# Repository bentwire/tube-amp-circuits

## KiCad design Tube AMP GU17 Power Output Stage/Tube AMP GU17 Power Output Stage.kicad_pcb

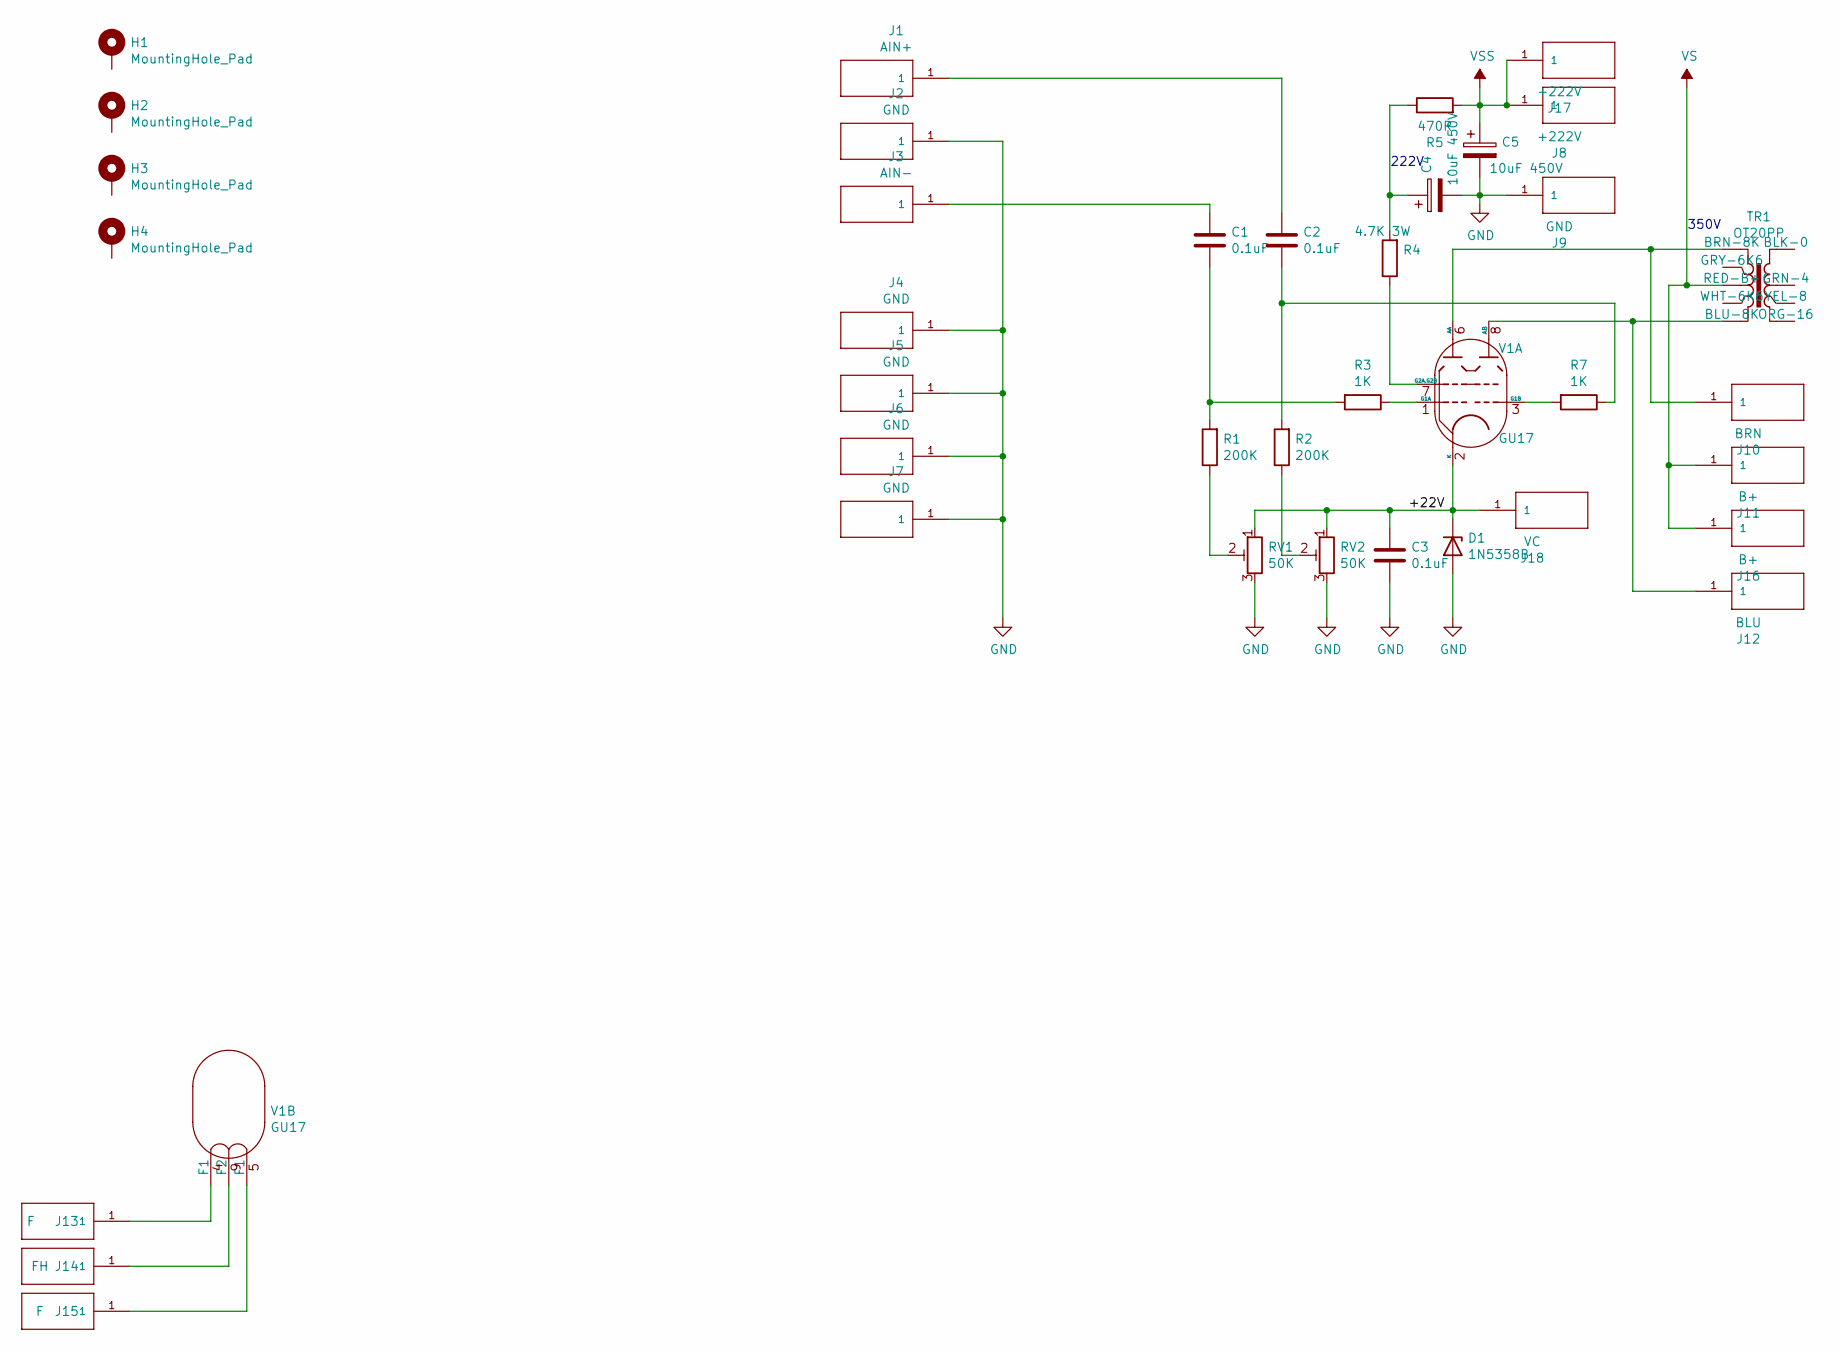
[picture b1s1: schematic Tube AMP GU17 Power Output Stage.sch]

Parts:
C1, C2, C3: 0.1uF; C_Rect_L7.2mm_W2.5mm_P5.00mm_FKS2_FKP2_MKS2_MKP2; MPN MKS2D031001A00MSSD
C4, C5: 10uF 450V; CP_Radial_D12.5mm_P5.00mm; MPN UCS2W100MHD
D1: 1N5358B; D_DO-201_P15.24mm_Horizontal
H1, H2, H3, H4: MountingHole_Pad; MountingHole_3.2mm_M3_Pad_Via
J1: AIN+; MILMAX_2501-2-00-80-00-00-07-0
J2, J4, J5, J6, J7, J9: GND; MILMAX_2501-2-00-80-00-00-07-0
J3: AIN-; MILMAX_2501-2-00-80-00-00-07-0
J8, J17: +222V; MILMAX_2501-2-00-80-00-00-07-0
J10: BRN; MILMAX_2501-2-00-80-00-00-07-0
J11, J16: B+; MILMAX_2501-2-00-80-00-00-07-0
J12: BLU; MILMAX_2501-2-00-80-00-00-07-0
J13, J15: F; MILMAX_2501-2-00-80-00-00-07-0
J14: FH; MILMAX_2501-2-00-80-00-00-07-0
J18: VC; MILMAX_2501-2-00-80-00-00-07-0
R1, R2: 200K; R_Axial_DIN0207_L6.3mm_D2.5mm_P10.16mm_Horizontal
R3, R7: 1K; R_Axial_DIN0207_L6.3mm_D2.5mm_P10.16mm_Horizontal
R4: 4.7K 3W; R_Axial_DIN0414_L11.9mm_D4.5mm_P20.32mm_Horizontal
R5: 470R; R_Axial_DIN0414_L11.9mm_D4.5mm_P20.32mm_Horizontal
RV1, RV2: 50K; Potentiometer_Bourns_3296W_Vertical
TR1: OT20PP
V1: GU17; B9A-PCB-21

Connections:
/+22V: C3.1, D1.1 (K), J18.1, RV1.1, RV2.1, V1.2 (K)
GND: C3.2, C4.2, C5.2, D1.2 (A), J2.1, J4.1, J5.1, J6.1, J7.1, J9.1, RV1.3, RV2.3
unnamed: C1.1, J3.1
unnamed: C1.2, R1.2, R3.2
unnamed: C2.1, J1.1
unnamed: C2.2, R2.2, R7.1
unnamed: C4.1, R4.2, R5.1
unnamed: J10.1, TR1.1 (BRN-8K), V1.6 (AA)
unnamed: J12.1, TR1.5 (BLU-8K), V1.8 (AB)
unnamed: J13.1, V1.4 (F1)
unnamed: J14.1, V1.9 (F2)
unnamed: J15.1, V1.5 (F1)
unnamed: R1.1, RV1.2
unnamed: R2.1, RV2.2
unnamed: R3.1, V1.1 (G1A)
unnamed: R4.1, V1.7 (G2A,G2B)
unnamed: R7.2, V1.3 (G1B)
VS: J11.1, J16.1, TR1.3 (RED-B+)
VSS: C5.1, J8.1, J17.1, R5.2

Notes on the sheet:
222V
350V

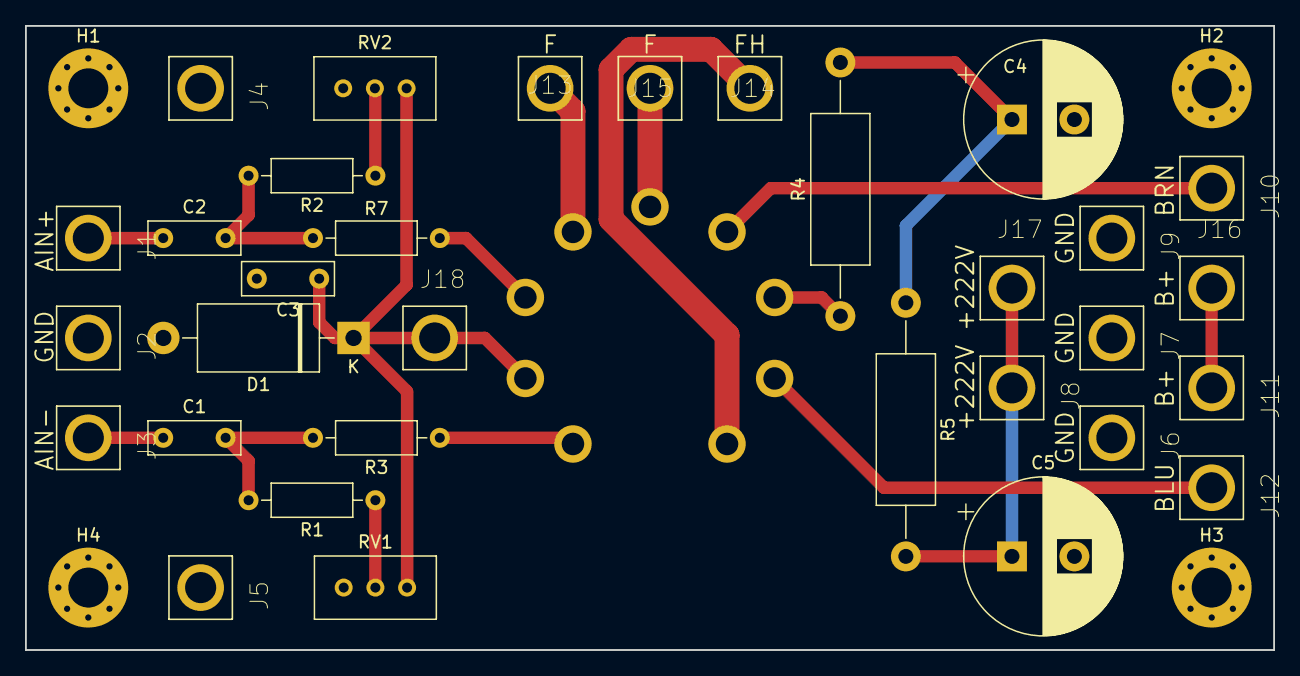
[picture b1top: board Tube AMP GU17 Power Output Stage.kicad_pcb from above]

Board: 2 copper layers, 100.0 x 50.0 mm, 37 parts (1 on the bottom side), 19 nets.

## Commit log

2020-09-02 Initial import
2020-09-04 Update to a new socket
